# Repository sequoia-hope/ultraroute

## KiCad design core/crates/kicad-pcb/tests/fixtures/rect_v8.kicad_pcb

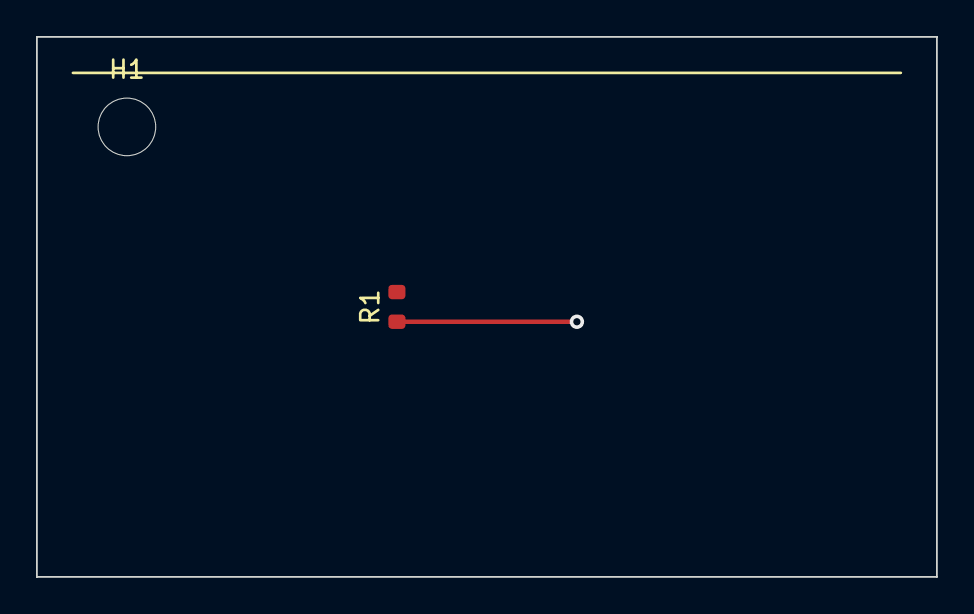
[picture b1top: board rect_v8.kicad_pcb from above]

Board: 2 copper layers, 50.0 x 30.0 mm, 3 parts (1 on the bottom side), 2 nets.

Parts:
C1: 100n; C_0805_2012Metric
H1: MountingHole; MountingHole_3.2mm
R1: 10k; R_0603_1608Metric

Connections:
GND: C1.2, R1.1
VCC: C1.1, R1.2

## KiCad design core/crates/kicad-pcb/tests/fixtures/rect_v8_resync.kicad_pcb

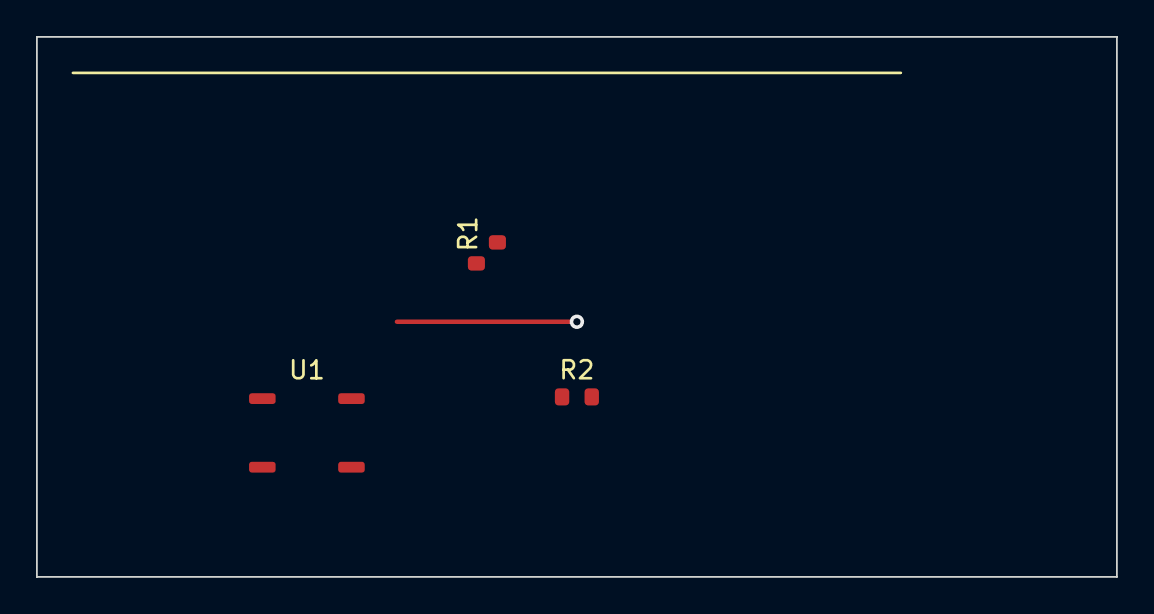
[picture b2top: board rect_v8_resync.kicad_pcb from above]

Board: 2 copper layers, 60.0 x 30.0 mm, 4 parts (1 on the bottom side), 2 nets.

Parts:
C1: 220n; C_0805_2012Metric
R1: 10k; R_0603_1608Metric
R2: 4k7; R_0603_1608Metric
U1: LM358; SOIC-8_3.9x4.9mm_P1.27mm

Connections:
GND: C1.2, R1.1, R2.1, U1.1
VCC: C1.1, R1.2, R2.2, U1.8
